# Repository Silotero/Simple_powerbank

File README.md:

# Simple_powerbank
This is a portable battery bank capable of being charged and discharged at 15W.

The main IC is the MP2722. It does all the heavy lifting. It advertises that it can be sink or source, but mainly trying to be the source to make sure that phones never become sources for it (Retry source function). It takes care of device plugged in detection at the USB-C port and the unplugging of the device to stop the charge. It also is a buck-boost converter, that allows bucks the charge to be suitable for the batteries, as well as boosting the charge for the USB-C output. It can also detect many faults and advertise them to the Attiny404 microcontroller via I2C, after sending an interrupt signal on its interrupt pin.
There is and AP9101CK6 IC that takes care of battery overcharge, overdischarge and short.

The Attiny404 acts as an additional brain for the MP2722 unlocking more of its functions as well as creating a basic user interface. It operates 5 leds. 4 of them indicate the battery charge and the 5th one lights up to indicate if a problem has been detected by the MP2722.
Since the MP2722 has many registers that change how the device behaves, the Attiny404 must set them according to how the user wants the device to operate. At startup the microcontroller sets up all of the registers and then checks them periodically or after an interrupt to see if the device has for some reason reset. If it detects that it writes to the registers again.

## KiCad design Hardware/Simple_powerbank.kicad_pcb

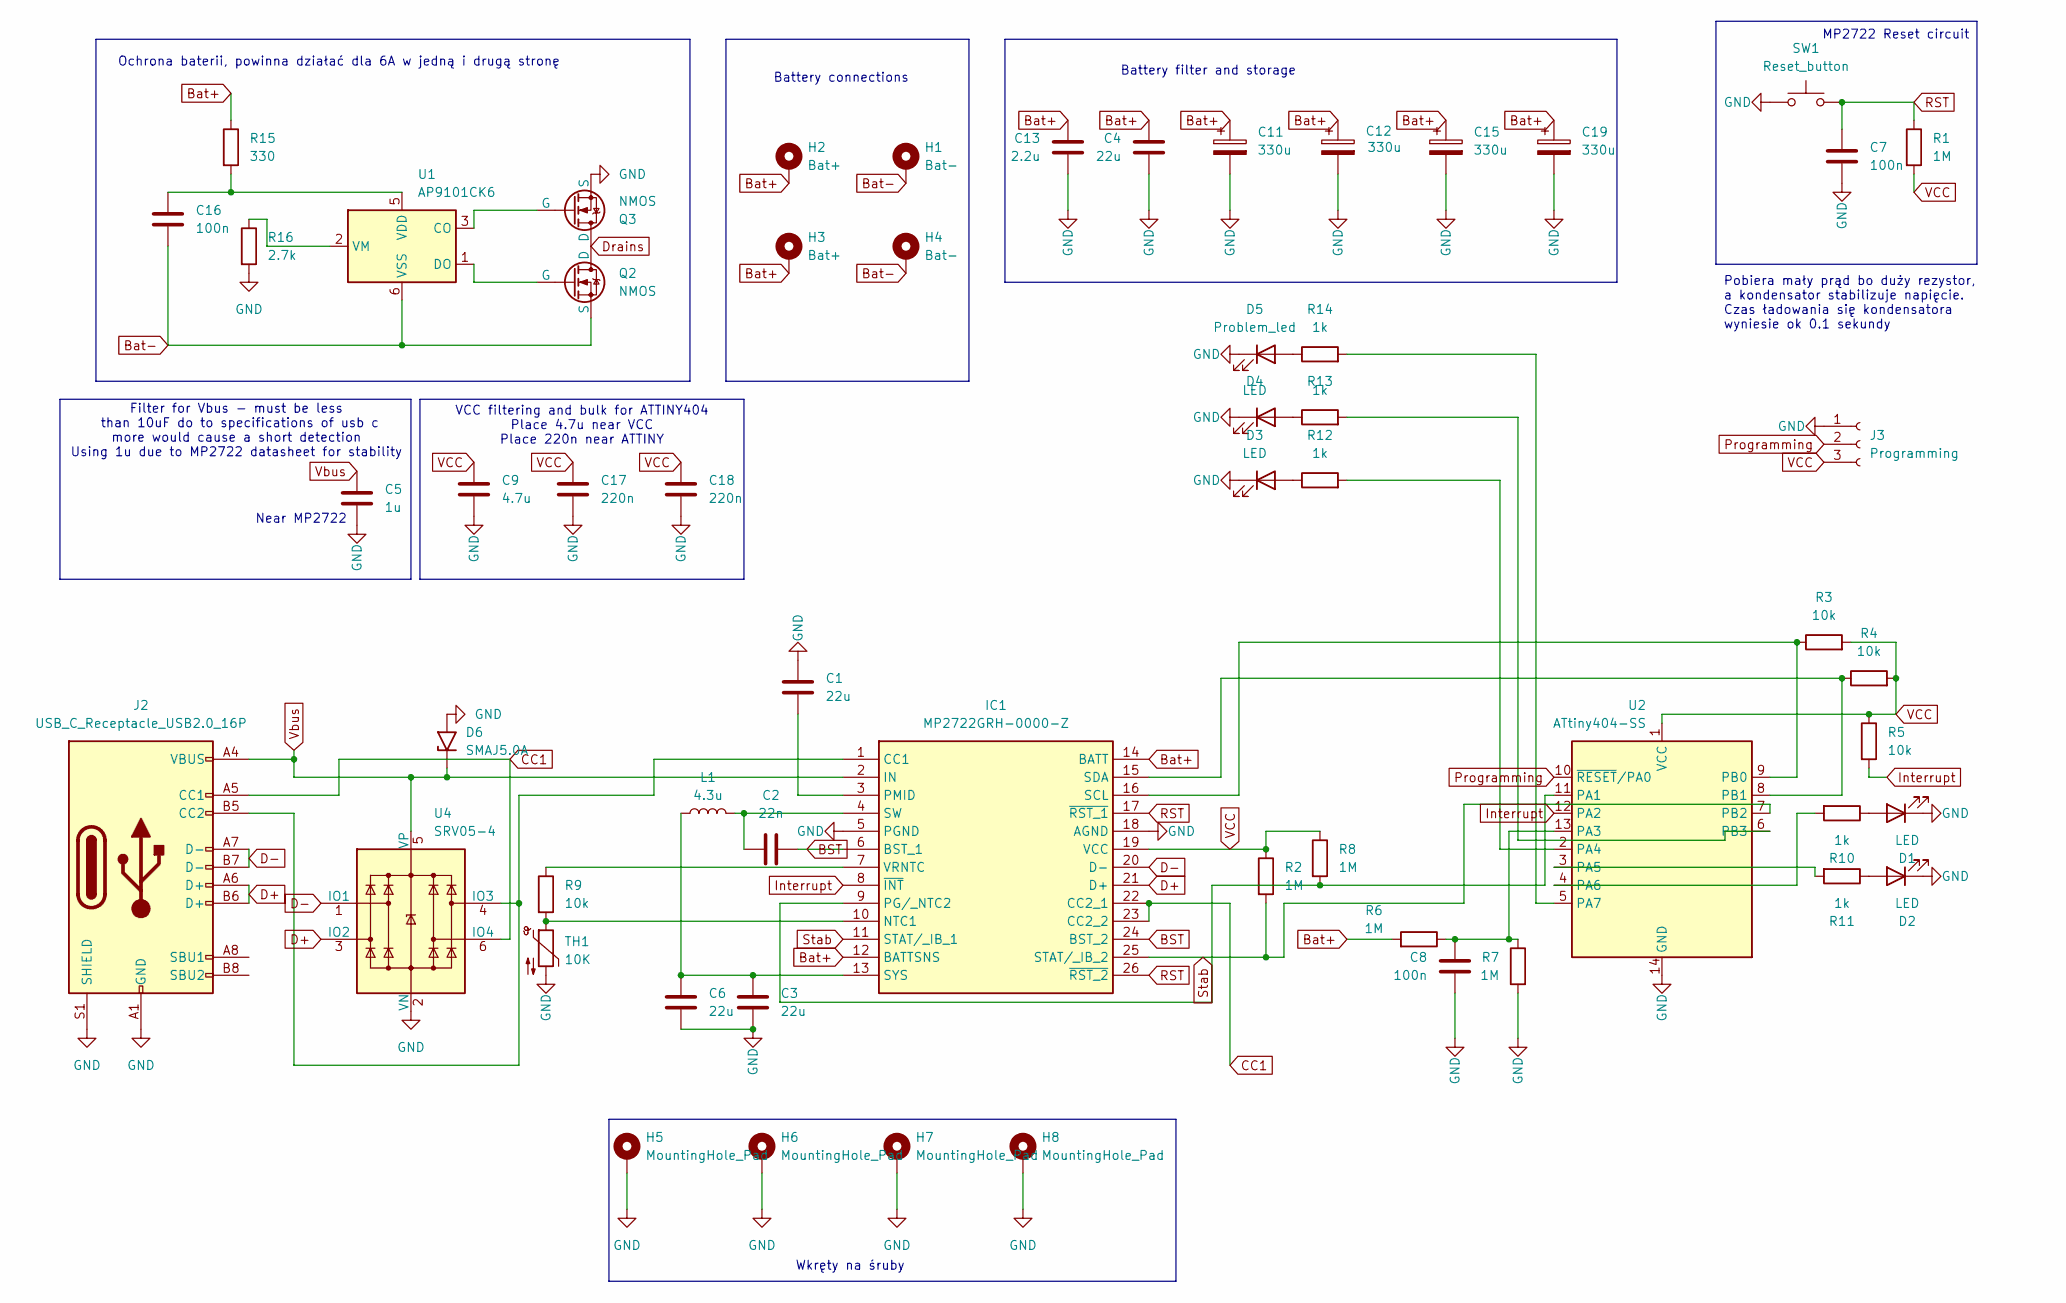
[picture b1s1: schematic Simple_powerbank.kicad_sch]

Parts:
C1, C3, C4, C6: 22u; C_0603_1608Metric
C2: 22n; C_0603_1608Metric
C5: 1u; C_0603_1608Metric
C7, C8, C16: 100n; C_0603_1608Metric
C9: 4.7u; C_0603_1608Metric
C11, C12, C15, C19: 330u; CP_Radial_D6.3mm_P2.50mm
C13: 2.2u; C_0603_1608Metric
C17, C18: 220n; C_0603_1608Metric
D1, D2, D3, D4: LED; LED_0603_1608Metric
D5: Problem_led; LED_0603_1608Metric
D6: SMAJ5.0A; D_SMA
H1, H4: Bat-; MountingHole_2.2mm_M2_DIN965_Pad_TopBottom
H2, H3: Bat+; MountingHole_2.2mm_M2_DIN965_Pad_TopBottom
H5, H6, H7, H8: MountingHole_Pad; MountingHole_2.2mm_M2_DIN965_Pad
IC1: MP2722GRH-0000-Z; MP2722GRH0000Z; Manufacturer_Part_Number MP2722GRH-0000-Z; Mouser Part Number 946-MP2722GRH-0000-Z
J2: USB_C_Receptacle_USB2.0_16P; USB_C_Receptacle_GCT_USB4105-xx-A_16P_TopMnt_Horizontal
J3: Programming; PinHeader_1x03_P2.54mm_Vertical
L1: 4.3u; L_10.4x10.4_H4.8
Q2, Q3: NMOS; SOP-8_3.76x4.96mm_P1.27mm
R1, R2, R6, R7, R8: 1M; R_0805_2012Metric
R3, R4, R5, R9: 10k; R_0805_2012Metric
R10, R11, R12, R13, R14: 1k; R_0805_2012Metric
R15: 330; R_0805_2012Metric
R16: 2.7k; R_0805_2012Metric
SW1: Reset_button; PinHeader_1x02_P1.27mm_Vertical
TH1: 10K; PinHeader_1x02_P1.27mm_Vertical
U1: AP9101CK6; SOT-23-6
U2: ATtiny404-SS; SOIC-14_3.9x8.7mm_P1.27mm
U4: SRV05-4; SOT-23-6

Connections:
BST: C2.2, IC1.6 (BST_1), IC1.24 (BST_2)
Bat+: C4.2, C11.1, C12.1, C13.2, C15.1, C19.1, H2.1, H3.1, IC1.12 (BATTSNS), IC1.14 (BATT), R6.2, R15.1
Bat-: C16.2, H1.1, H4.1, Q2.3 (S), U1.6 (VSS)
CC1: IC1.22 (CC2_1), IC1.23 (CC2_2), J2.A5 (CC1), U4.6 (IO4)
D+: IC1.21 (D+), J2.A6 (D+), J2.B6 (D+), U4.3 (IO2)
D-: IC1.20 (D-), J2.A7 (D-), J2.B7 (D-), U4.1 (IO1)
Drains: Q2.1 (D), Q3.1 (D)
GND: C1.1, C3.2, C4.1, C5.1, C6.2, C7.2, C8.2, C9.2, C11.2, C12.2, C13.1, C15.2, C17.2, C18.2, C19.2, D1.1 (K), D2.1 (K), D3.1 (K), D4.1 (K), D5.1 (K), D6.2 (A2), H5.1, H6.1, H7.1, H8.1, IC1.5 (PGND), IC1.18 (AGND), J2.A1 (GND), J2.A12 (GND), J2.B1 (GND), J2.B12 (GND), J2.S1 (SHIELD), J3.1, Q3.3 (S), R7.2, R16.2, SW1.1, TH1.2, U2.14 (GND), U4.2 (VN)
Interrupt: IC1.8 (~INT), R5.2, U2.12 (PA2)
unnamed: D1.2 (A), R10.1
unnamed: D2.2 (A), R11.1
unnamed: D3.2 (A), R12.1
unnamed: D4.2 (A), R13.1
unnamed: D5.2 (A), R14.1
unnamed: IC1.1 (CC1), J2.B5 (CC2), U4.4 (IO3)
unnamed: IC1.10 (NTC1), R9.2, TH1.1
unnamed: IC1.9 (PG/_NTC2), R8.2, U2.11 (PA1)
unnamed: C1.2, IC1.3 (PMID)
unnamed: IC1.16 (SCL), R3.1, U2.9 (PB0)
unnamed: IC1.15 (SDA), R4.1, U2.8 (PB1)
unnamed: C2.1, IC1.4 (SW), L1.2
unnamed: C3.1, C6.1, IC1.13 (SYS), L1.1
unnamed: IC1.7 (VRNTC), R9.1
unnamed: Q2.2 (G), U1.1 (DO)
unnamed: Q3.2 (G), U1.3 (CO)
unnamed: C16.1, R15.2, U1.5 (VDD)
unnamed: R16.1, U1.2 (VM)
unnamed: C8.1, R6.1, R7.1, U2.13 (PA3)
unnamed: R12.2, U2.2 (PA4)
unnamed: R11.2, U2.3 (PA5)
unnamed: R10.2, U2.4 (PA6)
unnamed: R14.2, U2.5 (PA7)
unnamed: R13.2, U2.6 (PB3)
Programming: J3.2, U2.10 (~RESET/PA0)
RST: C7.1, IC1.17 (~RST_1), IC1.26 (~RST_2), R1.1, SW1.2
Stab: IC1.11 (STAT/_IB_1), IC1.25 (STAT/_IB_2), R2.2, U2.7 (PB2)
VCC: C9.1, C17.1, C18.1, IC1.19 (VCC), J3.3, R1.2, R2.1, R3.2, R4.2, R5.1, R8.1, U2.1 (VCC)
Vbus: C5.2, D6.1 (A1), IC1.2 (IN), J2.A4 (VBUS), J2.A9 (VBUS), J2.B4 (VBUS), J2.B9 (VBUS), U4.5 (VP)

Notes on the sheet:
Battery filter and storage
Ochrona baterii, powinna działać dla 6A w jedną i drugą stronę
Wkręty na śruby
Battery connections
VCC filtering and bulk for ATTINY404 Place 4.7u near VCC Place 220n near ATTINY
MP2722 Reset circuit
Filter for Vbus - must be less than 10uF do to specifications of usb c more would cause a short detection Using 1u due to MP2722 datasheet for stability
Pobiera mały prąd bo duży rezystor, a kondensator stabilizuje napięcie. Czas ładowania się kondensatora wyniesie ok 0.1 sekundy
Near MP2722

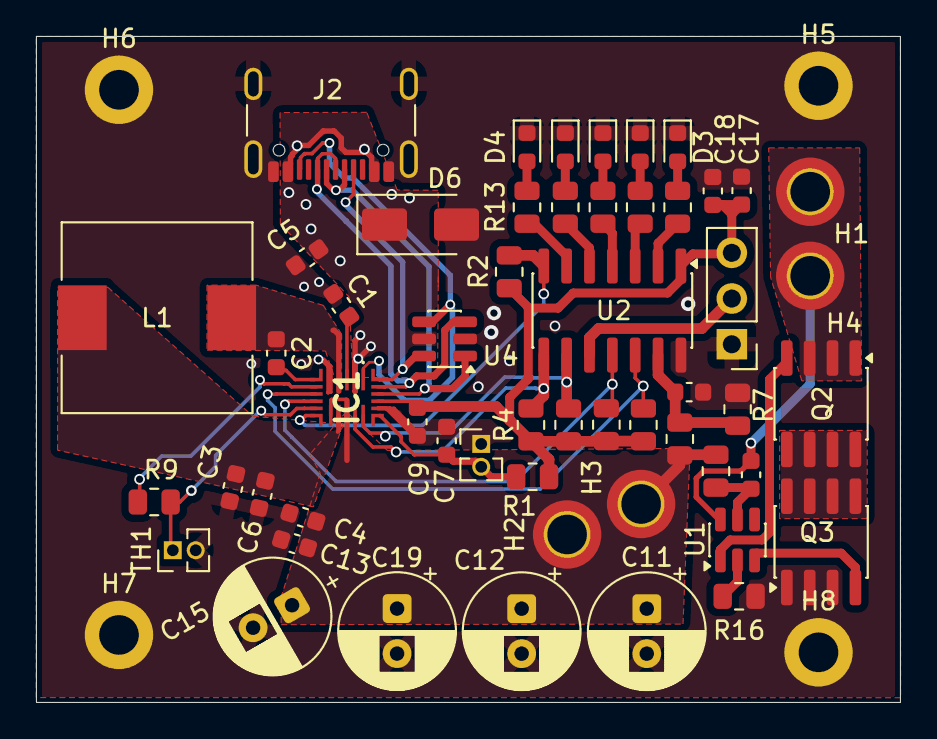
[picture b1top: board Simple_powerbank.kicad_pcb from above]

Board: 2 copper layers, 48.0 x 37.0 mm, 58 parts (0 on the bottom side), 38 nets.

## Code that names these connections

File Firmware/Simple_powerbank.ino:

#include "MP2722.h"
#include <avr/sleep.h>

MP2722 charger;
volatile bool eventDetected = false; // got an interrupt or not

bool faultDetected = false; // read a register, got fault/no fault, used for lighting up fault problem led

const int PIN_BATT  = PIN_PA3;  // Battery divider input
const int Battery_LED_PINS[] = {PIN_PB3, PIN_PA7, PIN_PA6, PIN_PA5}; // LED gpios
const int Problem_LED = PIN_PA4;

// Voltage levels for 1, 2, 3, 4 LEDs
const uint16_t BATT_THRESHOLDS[] = {696, 737, 778, 855}; // Pre-calculated ADC thresholds for: 3.4V, 3.6V, 3.8V, 4.18V

const unsigned long SWITCH_INTERVAL = 2500; // 2500 microseconds = 2.5ms
// Variables for Multiplexing
int currentLedIndex = 0;
unsigned long lastSwitchTime = 0;

// The Hardware ISR
// ISR = Interrupt Service Routine
// PORTA_PORT_vect = The hardware address for ANY interrupt on Port A
ISR(PORTA_PORT_vect) {
    // 1. Check WHICH pin fired (Critical if you have multiple interrupts on Port A)
    // We check if the Interrupt Flag (INTFLAGS) for Pin 2 is set.
    if (PORTA.INTFLAGS & PIN2_bm) {
        
        // 2. Your Logic
        eventDetected = true;

        // 3. Clear the Interrupt Flag (CRITICAL!)
        // Writing '1' to the flag bit actually clears it.
        // If you forget this, the interrupt will fire again immediately forever.
        PORTA.INTFLAGS = PIN2_bm; 
    }
}

void setup() {
    // 1. Setup Interrupt Pin (FALLING EDGE is mandatory for Pulse)
    Wire.begin();
    //PORTB.DIRSET = PIN2_bm; // stat pin, read to find out if  pinB2
    PORTA.DIRCLR = PIN2_bm; // Assuming INT is on PA2
    PORTA.PIN2CTRL = PORT_ISC_FALLING_gc; // to read the falling edge on interrupt pin

    PORTA.DIRSET = PIN5_bm | PIN6_bm | PIN7_bm;
    PORTB.DIRSET = PIN3_bm; // Setting up the leds pins as outputs

    PORTA.OUTCLR = PIN5_bm | PIN6_bm | PIN7_bm;
    PORTB.OUTCLR = PIN3_bm; // Setting low output for the led pins

    PORTA.DIRSET = PIN4_bm; // Problem led pin as output PIN_PA4
    VPORTA.OUT &= ~PIN4_bm; // set problem led pin output to low

    PORTA.DIRCLR = PIN3_bm; // PIN_PA3 set as input, for reading battery voltage divider
    // 1. Set Voltage Reference to Internal 2.5V
    // (Replaces analogReference(INTERNAL2V5))
    VREF.CTRLA |= VREF_ADC0REFSEL_2V5_gc;
    // 2. Configure the ADC Prescaler
    // We want the ADC clock to be between 50kHz and 1.5MHz.
    // Assuming 20MHz CPU clock, DIV32 gives ~625kHz (Perfect).
    ADC0.CTRLC = ADC_PRESC_DIV32_gc; // or DIV16_gc if running at 10MHz
    // 3. Enable the ADC (10-bit resolution is default)
    ADC0.CTRLA = ADC_ENABLE_bm | ADC_RESSEL_10BIT_gc;

    // 2. Start Charger
    if (charger.wasReset()) {
        charger.begin();
    }

    // setup the sleep workarounds of the attiny404
    set_sleep_mode(SLEEP_MODE_PWR_DOWN);
    sei();
    
}

void loop() {
    static unsigned long last_sleep_check = 0;
    showBatteryLevel();
    // 1. Handle Events
    if (eventDetected) {
        eventDetected = false;
        if (charger.processInterrupt()) {
            faultDetected = true;
        }
    }

    if (faultDetected) {
        digitalWrite(Problem_LED, (millis() / 250) % 2); // Fast blink
        if ((millis() / 250) % 10) {
            faultDetected = charger.checkFaultStatus();
        }
    }

    // 2. Periodically check "Canary" (in case Watchdog reset happened silently)
    static unsigned long lastCheck = 0;
    if (millis() - lastCheck > 10000) {
        if (charger.wasReset()) {
            charger.begin(); // Re-apply settings
        }
        lastCheck = millis();
    }
    
    if (!charger.isChargingDischarging() && millis() - last_sleep_check > 15000) {
        charger.gotosleep();
    }
}

void showBatteryLevel() {
    // 1. Read ADC
    // We take a few samples and average them to remove noise
    unsigned long currentMicros = micros();
    uint16_t rawSum = 0;
    for(uint8_t i = 0; i < 5; i++) {
        rawSum += readBatteryADC(); // Direct hardware read
        delay(2);
    }
    uint16_t rawAvg = rawSum / 5;

    // 3. Update LEDs
    // Workings of the battery indication: the leds gets cycled so only one is actually on at a time, the leds light up based on if the battery level is higher than the set level for the charge. If the charge is below 3.4 the first leds flickers
    if (currentMicros - lastSwitchTime >= SWITCH_INTERVAL) {
        lastSwitchTime = currentMicros;

        currentLedIndex++;
        if (currentLedIndex >= 4) {
            currentLedIndex = 0;
        }

        // 2. Clear ALL LEDs (Atomic & Fast)
        // Instead of looping to find which ones to turn off, just kill them all.
        // (Assuming LEDs are on PA4, PA5, PB0, PB1 - update if different!)
        PORTA.OUTCLR = PIN4_bm | PIN5_bm;
        PORTB.OUTCLR = PIN0_bm | PIN1_bm;

        // 3. Logic: Should the CURRENT LED be ON?
        bool shouldTurnOn = false;

        // SPECIAL CASE: Critical Low Battery (Blink LED 0)
        if (currentLedIndex == 0 && rawAvg < 696) {
            // ">> 8" divides by 256. "& 1" keeps the last bit (odd/even).
            // Result: A perfect ~256ms blink with NO division library.
            if ((millis() >> 8) & 1) shouldTurnOn = true;
        }
        // NORMAL CASE: Check Voltage Threshold
        else if (rawAvg >= BATT_THRESHOLDS[currentLedIndex]) {
            shouldTurnOn = true;
        }

        // 4. Execute: Turn ON the specific LED using VPORT
        if (shouldTurnOn) {
            switch (currentLedIndex) {
                case 0: VPORTA.OUT |= PIN4_bm; break; // PA4
                case 1: VPORTA.OUT |= PIN5_bm; break; // PA5
                case 2: VPORTB.OUT |= PIN0_bm; break; // PB0
                case 3: VPORTB.OUT |= PIN1_bm; break; // PB1
            }
        }
    }
}

uint16_t readBatteryADC() { // quick analog pin that can be used strictly for the one pin of my battery
    // 1. Select the Input Channel (AIN3 is PA3)
    ADC0.MUXPOS = ADC_MUXPOS_AIN3_gc; 

    // 2. Start Conversion
    ADC0.COMMAND = ADC_STCONV_bm; 

    // 3. Wait for result (Blocking, but very fast ~20us)
    while (!(ADC0.INTFLAGS & ADC_RESRDY_bm)); 

    // 4. Return the result
    return ADC0.RES; 
}

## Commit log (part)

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2026-04-07 Added finished project kicad files and the code files
2026-04-07 Changed firmware file structure
2026-05-22 Zmieniono wartości kondensatorów
